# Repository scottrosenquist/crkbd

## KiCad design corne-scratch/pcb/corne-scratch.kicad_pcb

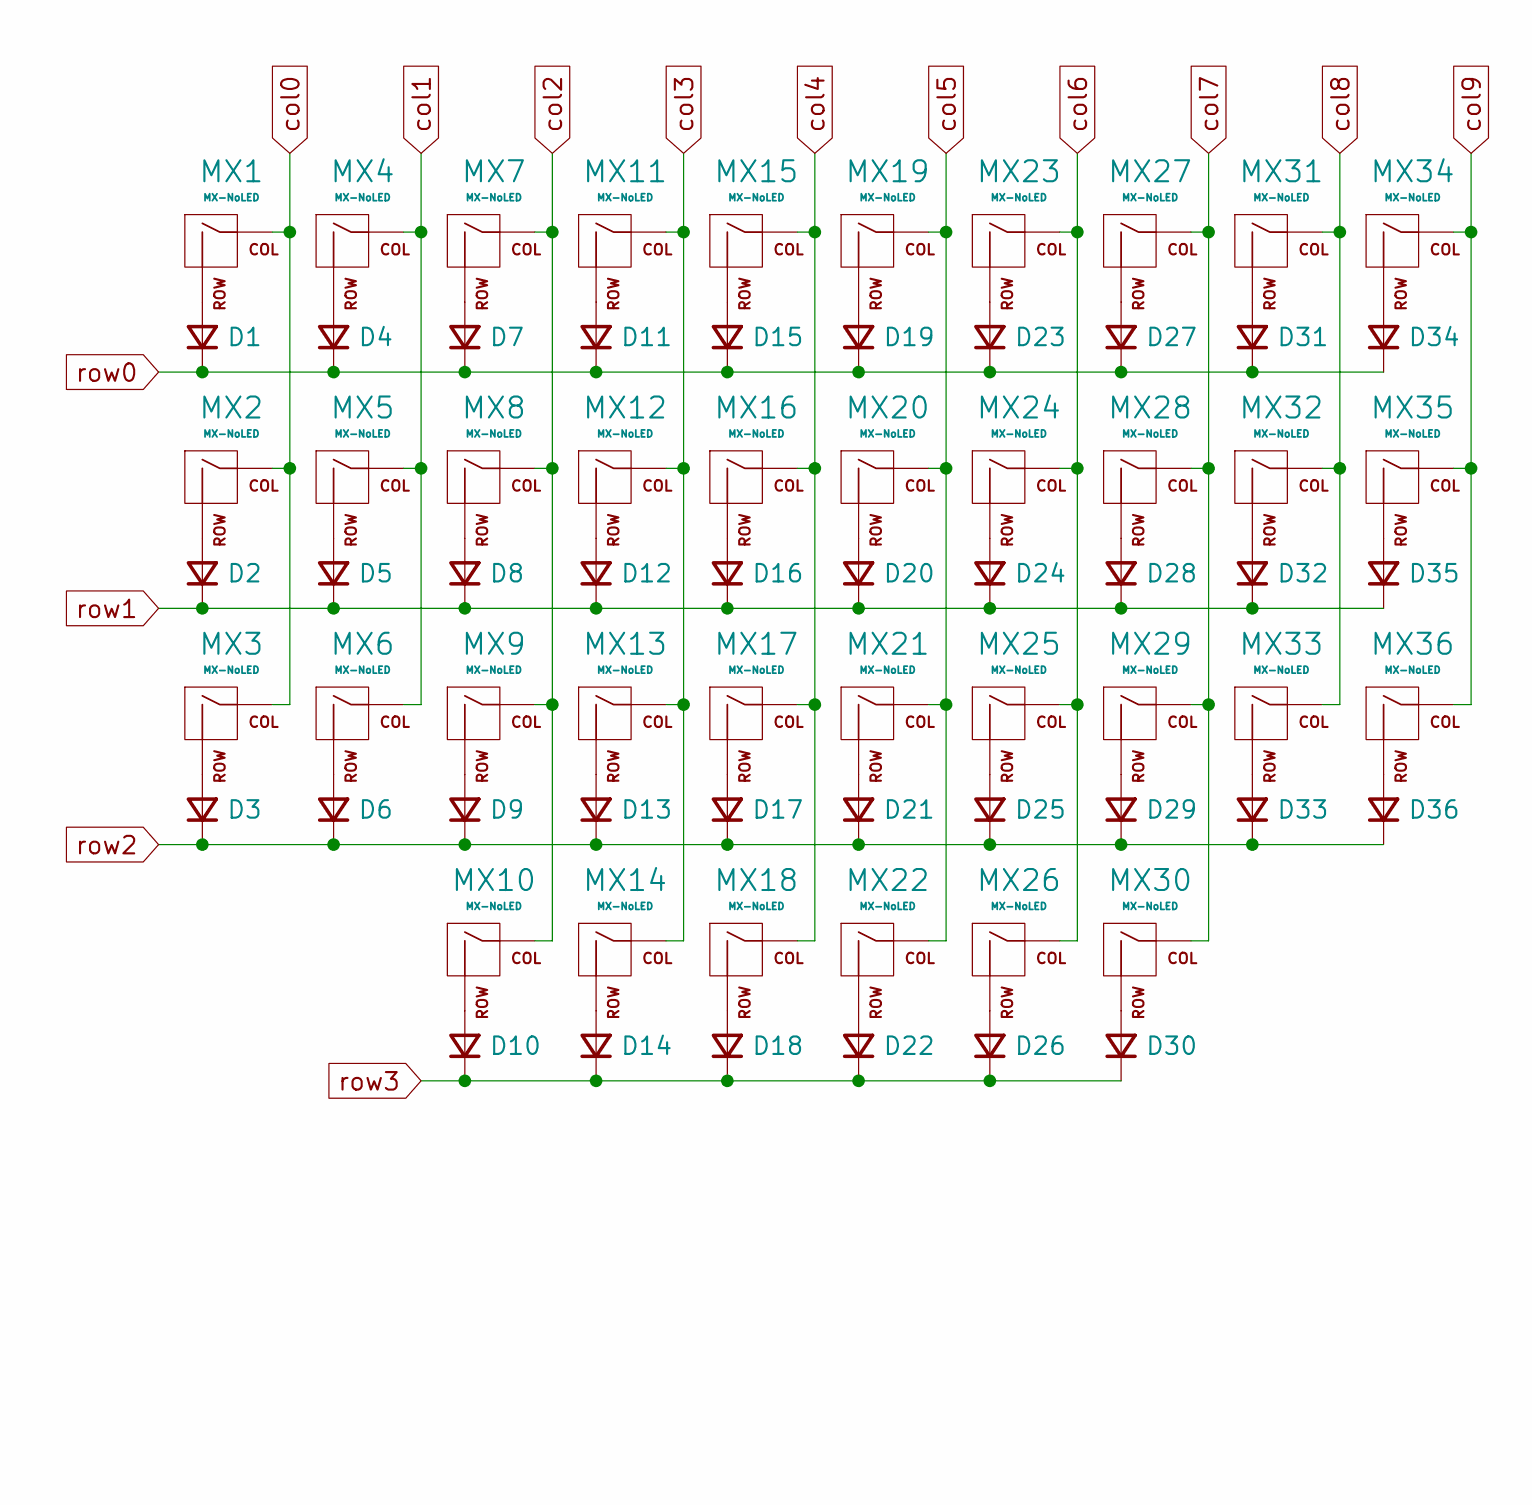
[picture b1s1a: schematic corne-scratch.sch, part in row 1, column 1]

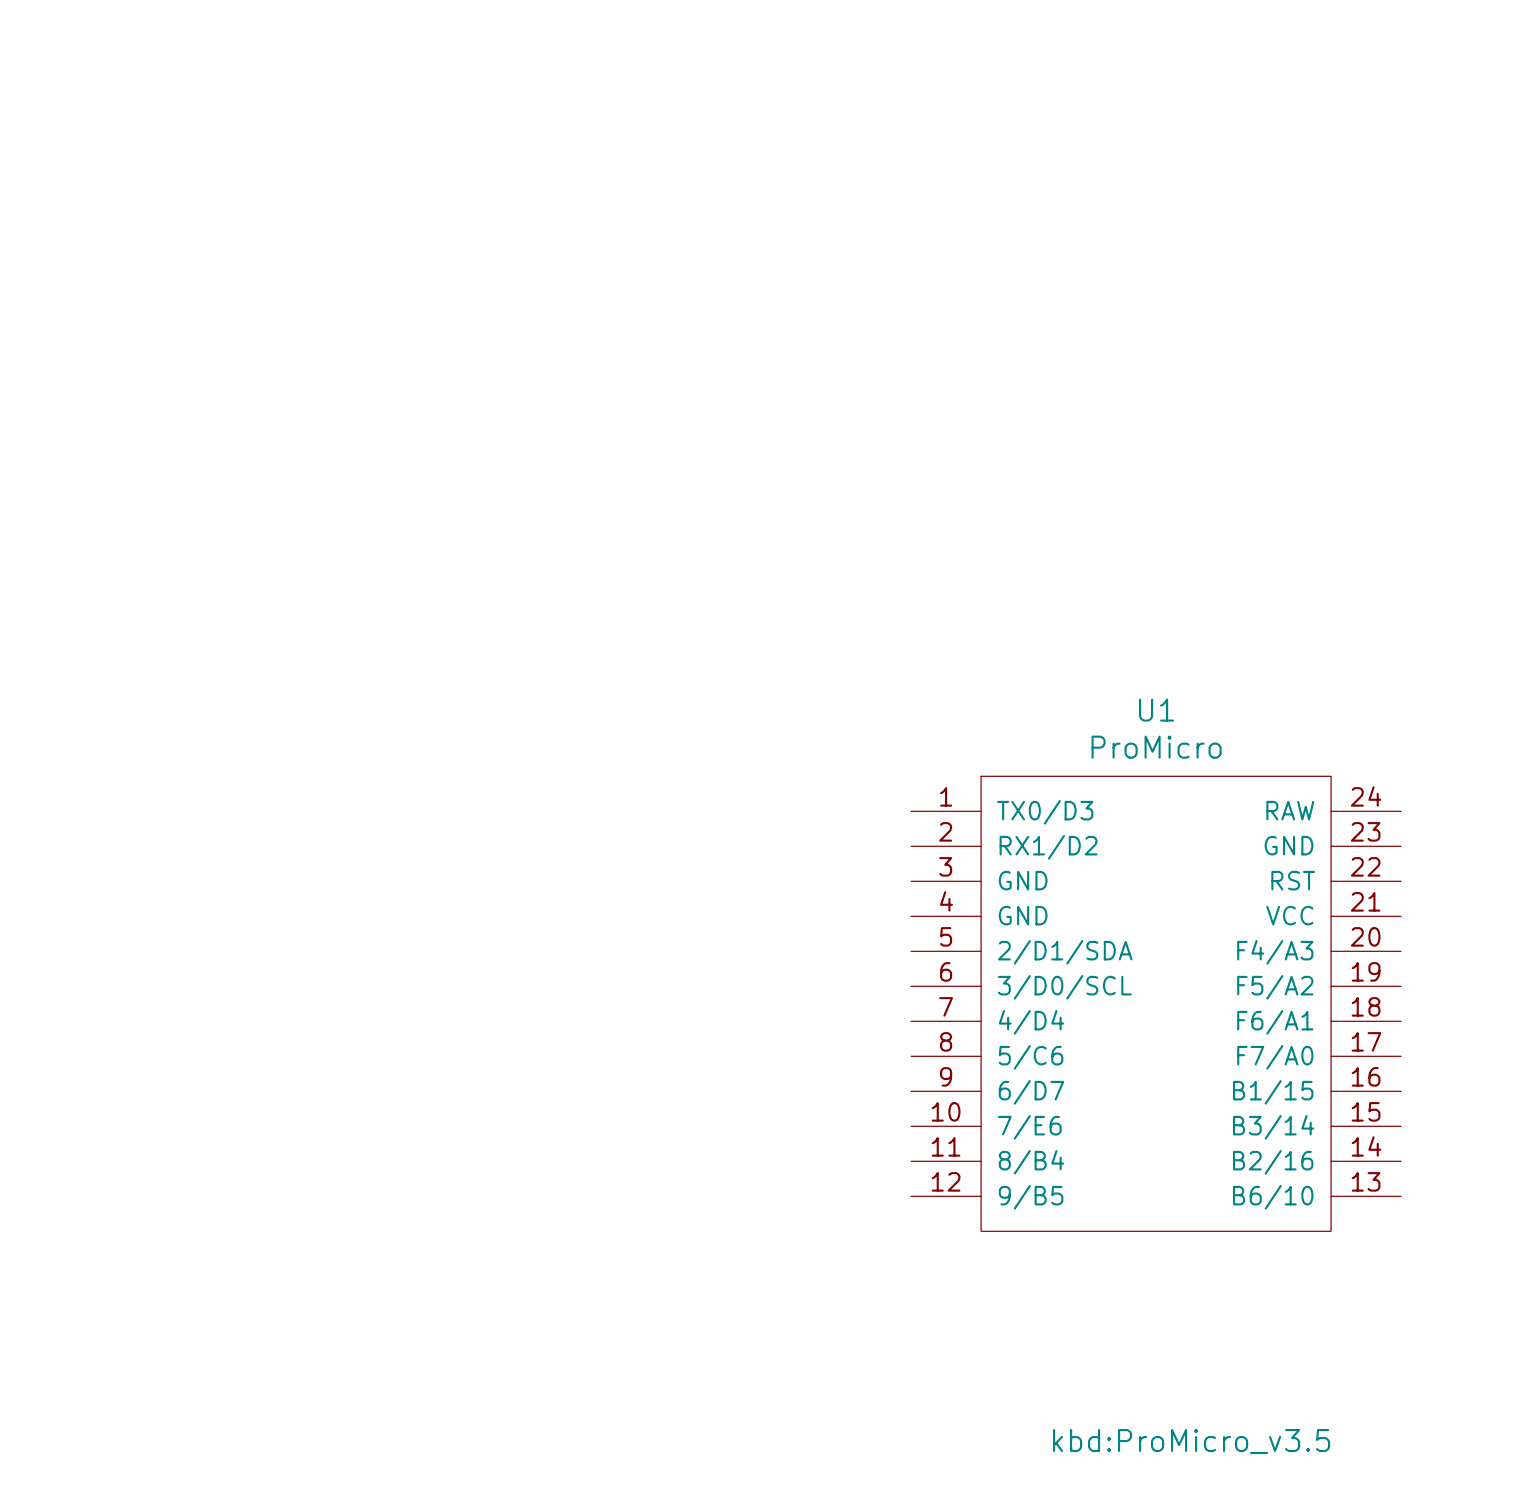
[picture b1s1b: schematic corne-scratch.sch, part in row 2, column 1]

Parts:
D1, D2, D3, D4, D5, D6, D7, D8, D9, D10, D11, D12, D13, D14, D15, D16, D17, D18, D19, D20, D21, D22, D23, D24, D25, D26, D27, D28, D29, D30, D31, D32, D33, D34, D35, D36: D_Small; D3_TH_1side
MX1, MX2, MX3, MX4, MX5, MX6, MX7, MX8, MX9, MX10, MX11, MX12, MX13, MX14, MX15, MX16, MX17, MX18: MX-NoLED; MXOnly-1U-Hotswap
MX19, MX20, MX21, MX22, MX23, MX24, MX25, MX26, MX27, MX28, MX29, MX30, MX31, MX32, MX33, MX34, MX35, MX36: MX-NoLED; MXOnly-1U-Hotswap-Polarity-Swap
U1: ProMicro; ProMicro_v3.5

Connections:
unnamed: D1.2 (A), MX1.2 (ROW)
unnamed: D2.2 (A), MX2.2 (ROW)
unnamed: D3.2 (A), MX3.2 (ROW)
unnamed: D4.2 (A), MX4.2 (ROW)
unnamed: D5.2 (A), MX5.2 (ROW)
unnamed: D6.2 (A), MX6.2 (ROW)
unnamed: D7.2 (A), MX7.2 (ROW)
unnamed: D8.2 (A), MX8.2 (ROW)
unnamed: D9.2 (A), MX9.2 (ROW)
unnamed: D10.2 (A), MX10.2 (ROW)
unnamed: D11.2 (A), MX11.2 (ROW)
unnamed: D12.2 (A), MX12.2 (ROW)
unnamed: D13.2 (A), MX13.2 (ROW)
unnamed: D14.2 (A), MX14.2 (ROW)
unnamed: D15.2 (A), MX15.2 (ROW)
unnamed: D16.2 (A), MX16.2 (ROW)
unnamed: D17.2 (A), MX17.2 (ROW)
unnamed: D18.2 (A), MX18.2 (ROW)
unnamed: D19.2 (A), MX19.2 (ROW)
unnamed: D20.2 (A), MX20.2 (ROW)
unnamed: D21.2 (A), MX21.2 (ROW)
unnamed: D22.2 (A), MX22.2 (ROW)
unnamed: D23.2 (A), MX23.2 (ROW)
unnamed: D24.2 (A), MX24.2 (ROW)
unnamed: D25.2 (A), MX25.2 (ROW)
unnamed: D26.2 (A), MX26.2 (ROW)
unnamed: D27.2 (A), MX27.2 (ROW)
unnamed: D28.2 (A), MX28.2 (ROW)
unnamed: D29.2 (A), MX29.2 (ROW)
unnamed: D30.2 (A), MX30.2 (ROW)
unnamed: D31.2 (A), MX31.2 (ROW)
unnamed: D32.2 (A), MX32.2 (ROW)
unnamed: D33.2 (A), MX33.2 (ROW)
unnamed: D34.2 (A), MX34.2 (ROW)
unnamed: D35.2 (A), MX35.2 (ROW)
unnamed: D36.2 (A), MX36.2 (ROW)
col0: MX1.1 (COL), MX2.1 (COL), MX3.1 (COL)
col1: MX4.1 (COL), MX5.1 (COL), MX6.1 (COL)
col2: MX7.1 (COL), MX8.1 (COL), MX9.1 (COL), MX10.1 (COL)
col3: MX11.1 (COL), MX12.1 (COL), MX13.1 (COL), MX14.1 (COL)
col4: MX15.1 (COL), MX16.1 (COL), MX17.1 (COL), MX18.1 (COL)
col5: MX19.1 (COL), MX20.1 (COL), MX21.1 (COL), MX22.1 (COL)
col6: MX23.1 (COL), MX24.1 (COL), MX25.1 (COL), MX26.1 (COL)
col7: MX27.1 (COL), MX28.1 (COL), MX29.1 (COL), MX30.1 (COL)
col8: MX31.1 (COL), MX32.1 (COL), MX33.1 (COL)
col9: MX34.1 (COL), MX35.1 (COL), MX36.1 (COL)
row0: D1.1 (K), D4.1 (K), D7.1 (K), D11.1 (K), D15.1 (K), D19.1 (K), D23.1 (K), D27.1 (K), D31.1 (K), D34.1 (K)
row1: D2.1 (K), D5.1 (K), D8.1 (K), D12.1 (K), D16.1 (K), D20.1 (K), D24.1 (K), D28.1 (K), D32.1 (K), D35.1 (K)
row2: D3.1 (K), D6.1 (K), D9.1 (K), D13.1 (K), D17.1 (K), D21.1 (K), D25.1 (K), D29.1 (K), D33.1 (K), D36.1 (K)
row3: D10.1 (K), D14.1 (K), D18.1 (K), D22.1 (K), D26.1 (K), D30.1 (K)

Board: 2 copper layers, 73 parts (36 on the bottom side), 50 nets, no tracks yet.

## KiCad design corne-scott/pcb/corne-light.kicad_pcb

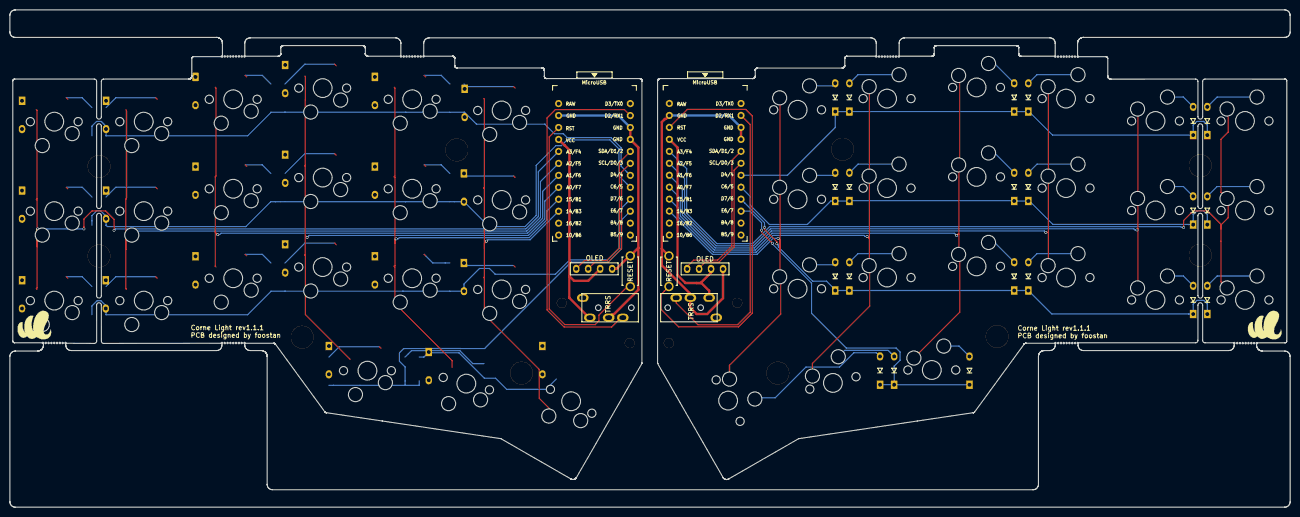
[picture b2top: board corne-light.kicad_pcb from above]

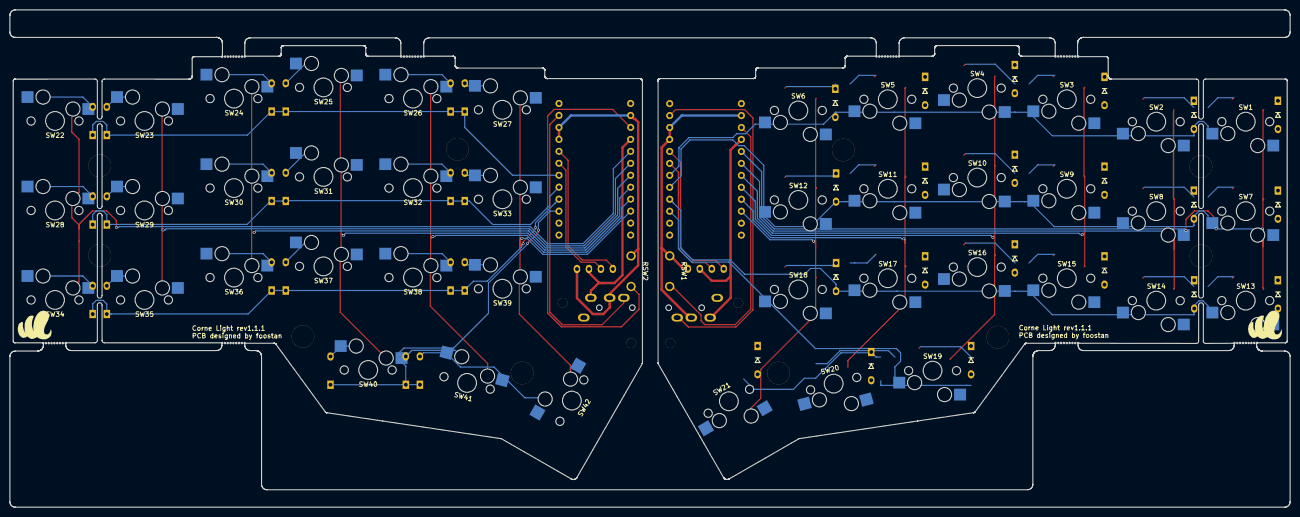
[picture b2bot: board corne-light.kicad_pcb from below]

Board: 2 copper layers, 271.8 x 105.6 mm, 114 parts (28 on the bottom side), 74 nets.

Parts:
D1, D2, D3, D4, D5, D6, D7, D8, D9, D10, D11, D12, D13, D14, D15, D16, D17, D18, D19, D20, D21, D22, D23, D24, D25, D26, D27, D28, D29, D30, D31, D32, D33, D34, D35, D36, D37, D38, D39, D40, D41, D42: D; D3_TH
J1, J6: MJ-4PP-9; MJ-4PP-9_1side
J2, J7: OLED; OLED_1side
J5, J5#2, J5#3, J5#4, J5#5, J5#6, J5#7, J5#8: Breakaway_Tabs; breakaway-mousebites
RSW1, RSW2: SW_PUSH; ResetSW_1side
Ref**: Val**; M2_Threads_v2
Ref**#2, Ref**#3, Ref**#4: Val**; M2_Threads_v2
Ref**#5, Ref**#6, Ref**#7, Ref**#8, Ref**#9, Ref**#10, Ref**#11, Ref**#12, Ref**#13, Ref**#14: Val**; M2_HOLE_v2
SW1, SW2, SW3, SW4, SW5, SW6, SW7, SW8, SW9, SW10, SW11, SW12, SW13, SW14, SW15, SW16, SW17, SW18, SW19, SW20, SW21, SW22, SW23, SW24, SW25, SW26, SW27, SW28, SW29, SW30, SW31, SW32, SW33, SW34, SW35, SW36, SW37, SW38, SW39, SW40, SW41, SW42: SW_PUSH; MXOnly-1U-Hotswap
U1, U2: ProMicro; ProMicro_v3

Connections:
GND: J1.C, J2.4, RSW1.2, U1.3, U1.4, U1.23
GNDA: J6.C, J7.1, RSW2.2, U2.3, U2.4, U2.23
unnamed: D1.2, SW1.2
unnamed: D2.2, SW2.2
unnamed: D3.2, SW3.2
unnamed: D4.2, SW4.2
unnamed: D5.2, SW5.2
unnamed: D6.2, SW6.2
unnamed: D7.2, SW7.2
unnamed: D8.2, SW8.2
unnamed: D9.2, SW9.2
unnamed: D10.2, SW10.2
unnamed: D11.2, SW11.2
unnamed: D12.2, SW12.2
unnamed: D13.2, SW13.2
unnamed: D14.2, SW14.2
unnamed: D15.2, SW15.2
unnamed: D16.2, SW16.2
unnamed: D17.2, SW17.2
unnamed: D18.2, SW18.2
unnamed: D19.2, SW19.2
unnamed: D20.2, SW20.2
unnamed: D21.2, SW21.2
unnamed: D22.2, SW22.2
unnamed: D23.2, SW23.2
unnamed: D24.2, SW24.2
unnamed: D25.2, SW25.2
unnamed: D26.2, SW26.2
unnamed: D27.2, SW27.2
unnamed: D28.2, SW28.2
unnamed: D29.2, SW29.2
unnamed: D30.2, SW30.2
unnamed: D31.2, SW31.2
unnamed: D32.2, SW32.2
unnamed: D33.2, SW33.2
unnamed: D34.2, SW34.2
unnamed: D35.2, SW35.2
unnamed: D36.2, SW36.2
unnamed: D37.2, SW37.2
unnamed: D38.2, SW38.2
unnamed: D39.2, SW39.2
unnamed: D40.2, SW40.2
unnamed: D41.2, SW41.2
unnamed: D42.2, SW42.2
SCL: J2.2, U1.6
SCL_r: J7.3, U2.6
SDA: J2.1, U1.5
SDA_r: J7.4, U2.5
VCC: J1.D, J2.3, U1.21
VDD: J6.D, J7.2, U2.21
col0: SW1.1, SW7.1, SW13.1, U1.20
col0_r: SW22.1, SW28.1, SW34.1, U2.20
col1: SW2.1, SW8.1, SW14.1, U1.19
col1_r: SW23.1, SW29.1, SW35.1, U2.19
col2: SW3.1, SW9.1, SW15.1, U1.18
col2_r: SW24.1, SW30.1, SW36.1, U2.18
col3: SW4.1, SW10.1, SW16.1, SW19.1, U1.17
col3_r: SW25.1, SW31.1, SW37.1, SW40.1, U2.17
col4: SW5.1, SW11.1, SW17.1, SW20.1, U1.16
col4_r: SW26.1, SW32.1, SW38.1, SW41.1, U2.16
col5: SW6.1, SW12.1, SW18.1, SW21.1, U1.15
col5_r: SW27.1, SW33.1, SW39.1, SW42.1, U2.15
data: J1.B, U1.2
data_r: J6.B, U2.2
reset: RSW1.1, U1.22
reset_r: RSW2.1, U2.22
row0: D1.1, D2.1, D3.1, D4.1, D5.1, D6.1, U1.7
row0_r: D22.1, D23.1, D24.1, D25.1, D26.1, D27.1, U2.7
row1: D7.1, D8.1, D9.1, D10.1, D11.1, D12.1, U1.8
row1_r: D28.1, D29.1, D30.1, D31.1, D32.1, D33.1, U2.8
row2: D13.1, D14.1, D15.1, D16.1, D17.1, D18.1, U1.9
row2_r: D34.1, D35.1, D36.1, D37.1, D38.1, D39.1, U2.9
row3: D19.1, D20.1, D21.1, U1.10
row3_r: D40.1, D41.1, D42.1, U2.10

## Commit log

2020-04-26 Initial commit-ish
2020-04-26 Remove outer row of switches
2020-04-27 Move through holes in
2020-04-27 Make switches hotswap
2020-04-27 Rotate left side switches and diodes
2020-04-27 Adjust left side diodes
2020-04-27 Add back reset switches I accidentally turned into mx switches
2021-05-03 Moving to another machine
